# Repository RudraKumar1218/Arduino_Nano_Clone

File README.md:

# Arduino Nano Design with KiCad PCB Editor

PCB Design of Arduino Nano made on KiCad using ECAD tools. Optimised thermally and electrically for material and processor protection.

Welcome to the repository for the Arduino Nano design implemented using KiCad PCB Editor. This project involves the creation of a PCB layout for the Arduino Nano, considering various factors such as cost reduction, high-power stability, thermal conduction, and voltage regulation.

## Overview

The Arduino Nano is a compact and versatile microcontroller board that is widely used in various electronics projects. This repository contains the KiCad PCB design files for the Arduino Nano, along with documentation detailing the design considerations and optimizations performed.

## Features

- Utilization of KiCad PCB Editor for designing the Arduino Nano PCB layout.
- Implementation of four-layer PCB design with two inner layers on FR4 substrate for optimal routing.
- Optimization of component placement to reduce costs and minimize cross-conduction for high-power stability.
- Tuning of track dimensions to minimize stray inductance and improve signal integrity.
- Consideration of thermal conduction strategies and voltage regulation techniques for ensuring material and processor protection.

## Design Considerations

- **Cost Reduction**: Efforts were made to optimize component placement to reduce manufacturing costs while maintaining functionality.
- **High-Power Stability**: Cross-conduction was minimized through careful routing and layout design to ensure stability under high-power conditions.
- **Signal Integrity**: Track dimensions were tuned to minimize stray inductance, enhancing the overall signal integrity of the board.
- **Thermal Management**: Thermal conduction strategies were considered to dissipate heat effectively and protect components from overheating.
- **Voltage Regulation**: Voltage regulation techniques were implemented to safeguard the material and processor from voltage fluctuations.

## Repository Structure

- **/ArduinoNano _Rudra_2021eeb1208/ArduinoNano_Gerber_BOM**: Contains Gerber files and bill of material
- **/Arduino_Nano_Clone.pdf** Contains a PDF report of the overall project

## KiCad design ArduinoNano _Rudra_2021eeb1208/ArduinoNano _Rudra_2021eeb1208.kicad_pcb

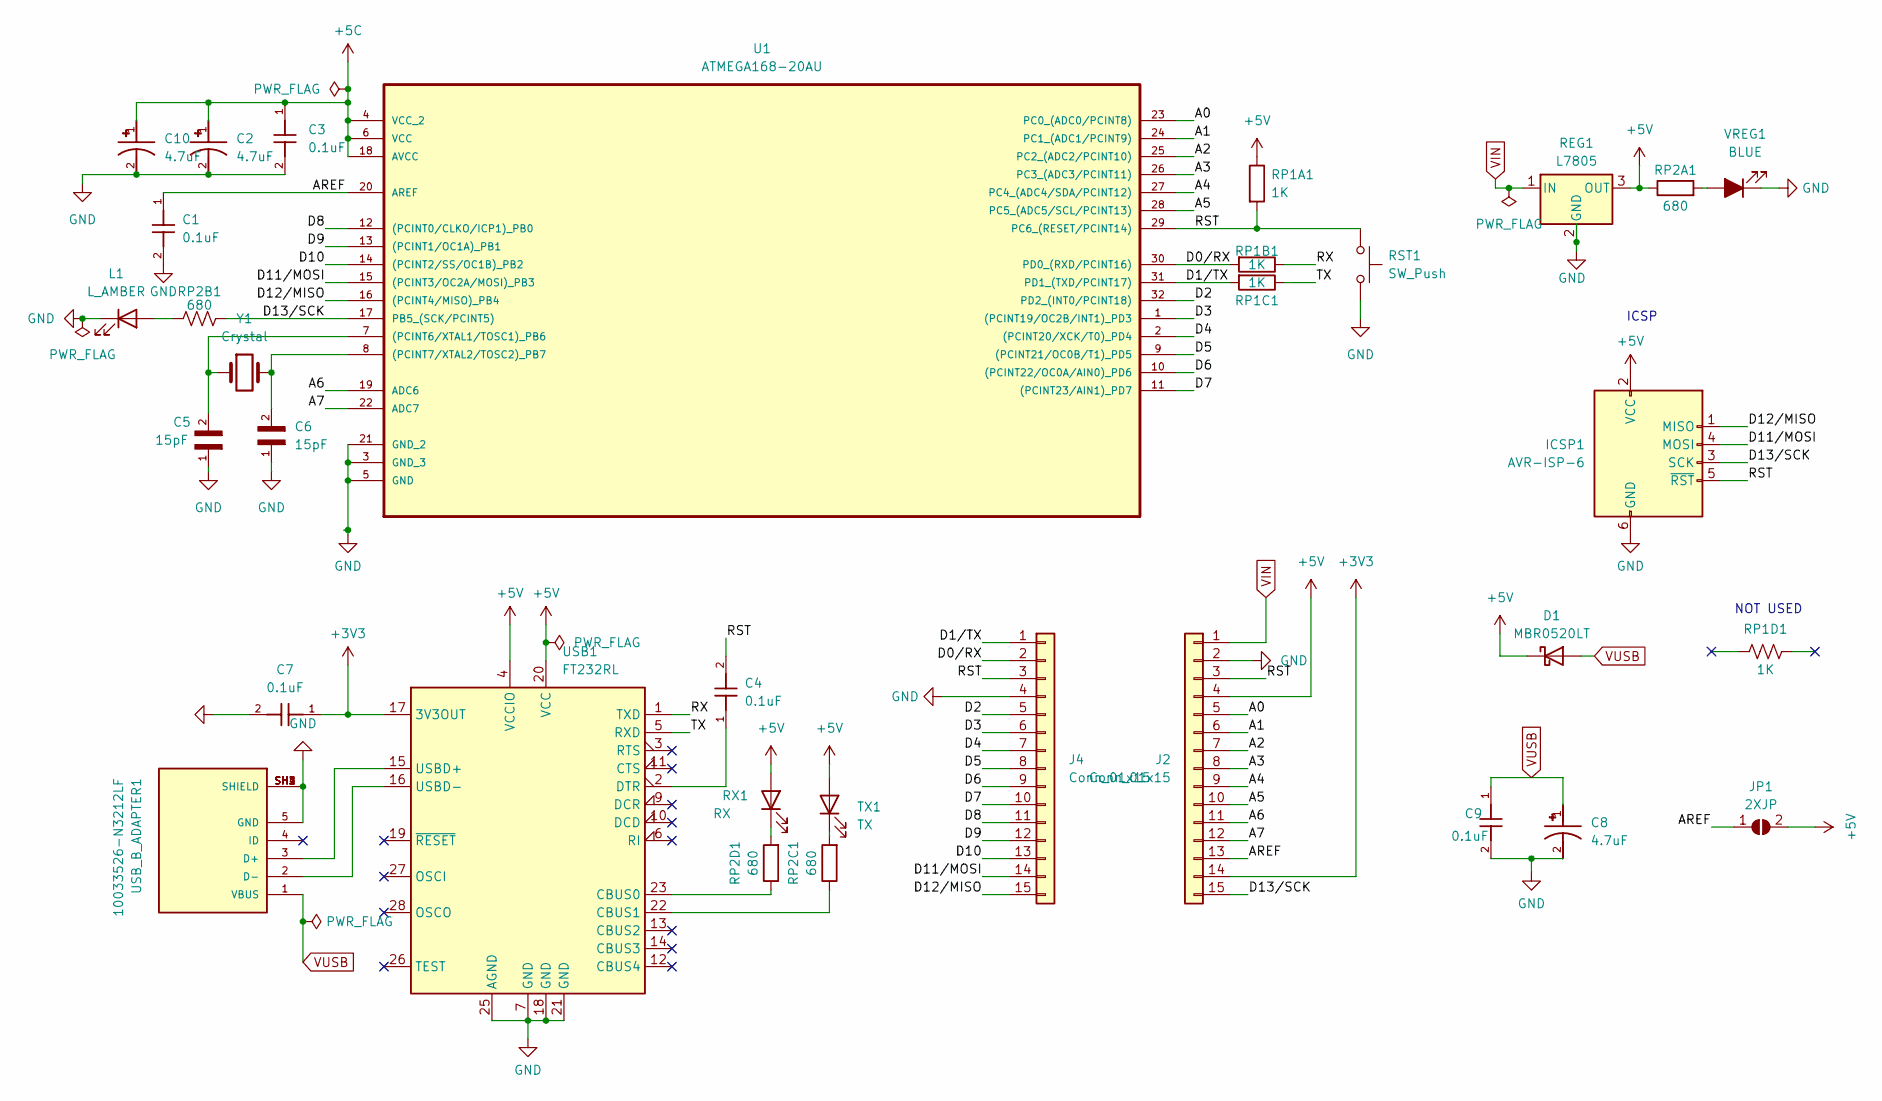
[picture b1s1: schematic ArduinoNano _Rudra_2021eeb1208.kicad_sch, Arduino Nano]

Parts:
C1, C3, C4, C7, C9: 0.1uF; CP_EIA-2012-12_Kemet-R
C2, C8, C10: 4.7uF; CP_EIA-2012-12_Kemet-R; PARTREV N/A
C5, C6: 15pF; CP_EIA-2012-12_Kemet-R
D1: MBR0520LT; D_SOD-123
ICSP1: AVR-ISP-6; PinHeader_2x03_P2.54mm_Vertical
J2, J4: Conn_01x15; PinHeader_1x15_P2.54mm_Vertical
JP1: 2XJP; SolderJumper-2_P1.3mm_Open_Pad1.0x1.5mm
L1: L_AMBER; LED_0805_2012Metric
REG1: L7805; SOT-223-3_TabPin2
RP1A1, RP1B1, RP1C1, RP1D1: 1K; R_0805_2012Metric
RP2A1, RP2B1, RP2C1, RP2D1: 680; R_0805_2012Metric
RST1: SW_Push; SW_SPST_B3U-1000P-B
RX1: RX; LED_0805_2012Metric
TX1: TX; LED_0805_2012Metric
U1: ATMEGA168-20AU; QFP80P900X900X120-32N; MPN ATMEGA168-20AU
USB1: FT232RL; SSOP-28_5.3x10.2mm_P0.65mm
USB_B_ADAPTER1: 10033526-N3212LF; AMPHENOL_10033526-N3212LF
VREG1: BLUE; LED_0805_2012Metric
Y1: Crystal; Crystal_HC49-4H_Vertical

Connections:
+3V3: C7.1, J2.14, USB1.17 (3V3OUT)
+5C: C2.1, C3.1, C10.1, U1.4 (VCC_2), U1.6 (VCC), U1.18 (AVCC)
+5V: D1.1 (K), ICSP1.2 (VCC), J2.4, JP1.2 (B), REG1.3 (OUT), RP1A1.1, RP2A1.1, RX1.2 (A), TX1.2 (A), USB1.4 (VCCIO), USB1.20 (VCC)
/A0: J2.5, U1.23 (PC0_(ADC0/PCINT8))
/A1: J2.6, U1.24 (PC1_(ADC1/PCINT9))
/A2: J2.7, U1.25 (PC2_(ADC2/PCINT10))
/A3: J2.8, U1.26 (PC3_(ADC3/PCINT11))
/A4: J2.9, U1.27 (PC4_(ADC4/SDA/PCINT12))
/A5: J2.10, U1.28 (PC5_(ADC5/SCL/PCINT13))
/A6: J2.11, U1.19 (ADC6)
/A7: J2.12, U1.22 (ADC7)
/AREF: C1.1, J2.13, JP1.1 (A), U1.20 (AREF)
/D0/RX: J4.2, RP1B1.2, U1.30 (PD0_(RXD/PCINT16))
/D1/TX: J4.1, RP1C1.2, U1.31 (PD1_(TXD/PCINT17))
/D2: J4.5, U1.32 (PD2_(INT0/PCINT18))
/D3: J4.6, U1.1 ((PCINT19/OC2B/INT1)_PD3)
/D4: J4.7, U1.2 ((PCINT20/XCK/T0)_PD4)
/D5: J4.8, U1.9 ((PCINT21/OC0B/T1)_PD5)
/D6: J4.9, U1.10 ((PCINT22/OC0A/AIN0)_PD6)
/D7: J4.10, U1.11 ((PCINT23/AIN1)_PD7)
/D8: J4.11, U1.12 ((PCINT0/CLKO/ICP1)_PB0)
/D9: J4.12, U1.13 ((PCINT1/OC1A)_PB1)
/D10: J4.13, U1.14 ((PCINT2/SS/OC1B)_PB2)
/D11/MOSI: ICSP1.4 (MOSI), J4.14, U1.15 ((PCINT3/OC2A/MOSI)_PB3)
/D12/MISO: ICSP1.1 (MISO), J4.15, U1.16 ((PCINT4/MISO)_PB4)
/D13/SCK: ICSP1.3 (SCK), J2.15, RP2B1.2, U1.17 (PB5_(SCK/PCINT5))
/RST: C4.2, ICSP1.5 (~RST), J2.3, J4.3, RP1A1.2, RST1.1, U1.29 (PC6_(RESET/PCINT14))
/RX: RP1B1.1, USB1.1 (TXD)
/TX: RP1C1.1, USB1.5 (RXD)
GND: C1.2, C2.2, C3.2, C5.1, C6.1, C7.2, C8.2, C9.2, C10.2, ICSP1.6 (GND), J2.2, J4.4, L1.1 (K), REG1.2 (GND), RST1.2, U1.3 (GND_3), U1.5 (GND), U1.21 (GND_2), USB1.7 (GND), USB1.18 (GND), USB1.21 (GND), USB1.25 (AGND), USB_B_ADAPTER1.5 (GND), USB_B_ADAPTER1.SH1 (SHIELD), USB_B_ADAPTER1.SH2 (SHIELD), USB_B_ADAPTER1.SH3 (SHIELD), USB_B_ADAPTER1.SH4 (SHIELD), VREG1.1 (K)
unnamed: L1.2 (A), RP2B1.1
unnamed: RP2D1.2, RX1.1 (K)
unnamed: RP2C1.2, TX1.1 (K)
unnamed: C5.2, U1.7 ((PCINT6/XTAL1/TOSC1)_PB6), Y1.1
unnamed: C6.2, U1.8 ((PCINT7/XTAL2/TOSC2)_PB7), Y1.2
unnamed: RP2D1.1, USB1.23 (CBUS0)
unnamed: RP2C1.1, USB1.22 (CBUS1)
unnamed: C4.1, USB1.2 (DTR)
unnamed: USB1.15 (USBD+), USB_B_ADAPTER1.3 (D+)
unnamed: USB1.16 (USBD-), USB_B_ADAPTER1.2 (D-)
unnamed: RP2A1.2, VREG1.2 (A)
VIN: J2.1, REG1.1 (IN)
VUSB: C8.1, C9.1, D1.2 (A), USB_B_ADAPTER1.1 (VBUS)

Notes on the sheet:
ICSP
NOT USED

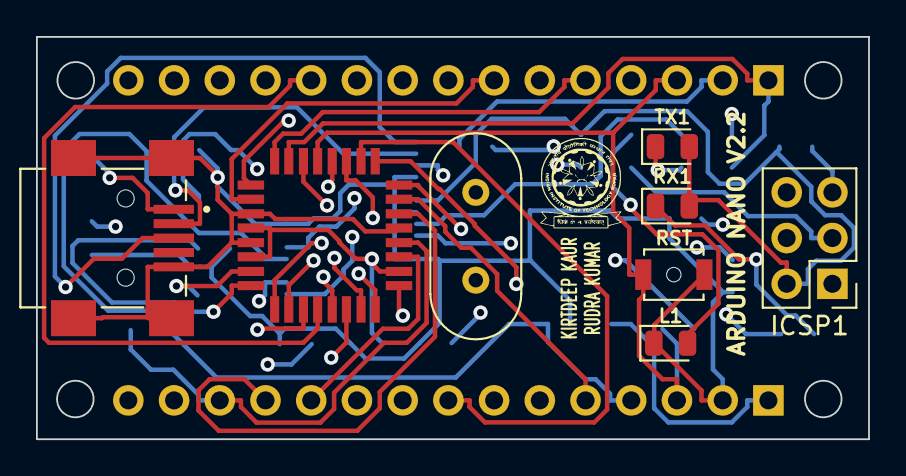
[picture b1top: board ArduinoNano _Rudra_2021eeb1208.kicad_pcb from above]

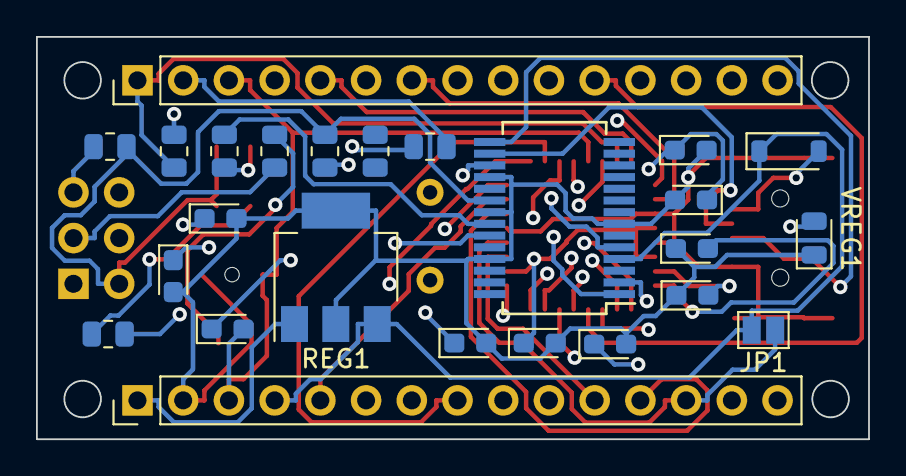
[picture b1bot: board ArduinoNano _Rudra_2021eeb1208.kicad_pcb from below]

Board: 4 copper layers, 46.2 x 22.4 mm, 33 parts (25 on the bottom side), 43 nets.

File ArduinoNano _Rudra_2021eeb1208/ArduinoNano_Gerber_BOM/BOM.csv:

"Id";"Designator";"Footprint";"Quantity";"Designation";"Supplier and ref";
1;"RST1";"SW_SPST_B3U-1000P-B";1;"SW_Push";;;
2;"ICSP1";"PinHeader_2x03_P2.54mm_Vertical";1;"AVR-ISP-6";;;
3;"L1";"LED_0805_2012Metric";1;"L_AMBER";;;
4;"RX1";"LED_0805_2012Metric";1;"RX";;;
5;"J7";"AMPHENOL_10033526-N3212LF";1;"10033526-N3212LF";;;
6;"TX1";"LED_0805_2012Metric";1;"TX";;;
7;"Y1";"Crystal_HC49-4H_Vertical";1;"Crystal";;;
8;"U1";"QFP80P900X900X120-32N";1;"ATMEGA168-20AU";;;
9;"REG1";"SOT-223-3_TabPin2";1;"L7805";;;
10;"C9,C3,C7,C4,C1";"CP_EIA-2012-12_Kemet-R";5;"0.1uF";;;
11;"C2,C10,C8";"CP_EIA-2012-12_Kemet-R";3;"4.7uF";;;
12;"VREG1";"LED_0805_2012Metric";1;"BLUE";;;
13;"RP1D1,RP1C1,RP1B1,RP1A1";"R_0805_2012Metric";4;"1K";;;
14;"C5,C6";"CP_EIA-2012-12_Kemet-R";2;"15pF";;;
15;"RP2C1,RP2A1,RP2B1,RP2D1";"R_0805_2012Metric";4;"680";;;
16;"D1";"D_SOD-123";1;"MBR0520LT";;;
17;"USB1";"SSOP-28_5.3x10.2mm_P0.65mm";1;"FT232RL";;;
18;"JP1";"SolderJumper-2_P1.3mm_Open_Pad1.0x1.5mm";1;"2XJP";;;
19;"J2,J4";"PinHeader_1x15_P2.54mm_Vertical";2;"Conn_01x15";;;

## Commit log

2024-03-11 README.md
